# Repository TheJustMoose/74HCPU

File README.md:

# 74HCPU

Not a very scary instruction set discrete logic processor.

* 8 bit data
* 16 bit address / 64KB RAM
* 17 bit address (in V register) / 128KW Dual Bank Video RAM
* 16 [instructions](#instruction-list)
* 8 data [registers](#registers) and 4 pointer registers in 2 banks
* 1 [flags register](#flags-register) in IO port
* 32 input ports and 32 output ports (You can write a constant to the first 8 ports. Only registers can be written to the remaining ports.)
* Assembled from 74HCxx series ICs!

## Soft!
[ASM](./ASM.md)
[UEMUL]()

## CPU structure

## How this CPU works?

[Layers of PCBs](layers/README.md)

## Instruction list
*The words 'instruction' and 'command' mean the same thing.*

```
|----------------------------------------------|f|-------------------------------------------------------------|
|   HIGH BYTE    |    LOW BYTE   |  HIGH BYTE  |l|                                                             |
|F E D C  B A 9 8 7 6 5 4 3 2 1 0|   (again)   |a|                    SHORT DESCRIPTION                        |
|   4   +   3 + 1 + 3  +    5    = 16          |g|                                                             |
|----------------------------------------------|s|-------------------------------------------------------------|
|   ADD |  DST |1|    CONST or   | 01 0000 0001|*| Add a constant to a register (This is one command, not two) |
|   ADD |  DST |0| SRC |-|Z|z|I|i| 00 0000 0000|*| Add a register to a register (same OpCode, different bit 8) |
|----------------------------------------------| |-------------------------------------------------------------|
|  ADDC |  DST |C| SRC |F|Z|z|I|i| 10 0001 0000|*| ADD a constant or register and CARRY FLAG to a register     |
|   AND |  DST |C| SRC |-|Z|z|I|i| 20 0010 0000|*| Bitwise AND a constant or register with a register          |
|    OR |  DST |C| SRC |-|Z|z|I|i| 30 0011 0000|*| Bitwise OR a constant or register with a register           |
|   XOR |  DST |C| SRC |-|Z|z|I|i| 40 0100 0000|*| Bitwise XOR a constant or register with a register          |
|   MUL |  DST |C| SRC |-|Z|z|I|i| 50 0101 0000|*| MULtiply a constant or register by a register.              |
|   UNO |  DST |0|-|TYP|F|-|-|-|-| 60 0110 0000|*| Unary commands INV, SWAP, LSR, LSRC                         |
|   MOV |  DST |C| SRC |*|Z|z|I|i| 70 0111 0000| | MOV a constant or register to a register                    |
|   LPM |  DST |0|EXT|D|U|-|-|-|W| 80 1000 0000| | Load Program Memory - Read data from [commands] ROM         |
|    LD |  DST |V|EXT|D|U|OFFSET4| 90 1001 0000| | LoaD data from RAM to a register                            |
|    IN |  DST |  PORT   |Z|z|I|i| A0 1010 0000| | INput data from port to a register                          |
|--------------|8-7-6-5-4|-------|-------------| |-------------------------------------------------------------|
|   OUT | PORT |1|    CONST or   | B1 1011 0001| | Output const to a port (This is one command, not two)       |
|   OUT | PORT |0| SRC |PRT|X|O|o| B0 1011 0000| | Output register to a port (same OpCode, different bit 8)    |
|----------------------------------------------| |-------------------------------------------------------------|
|    ST |  SRC |V|EXT|D|U|OFFSET4| C0 1100 0000| | STore a register to a RAM                                   |
|   CMP |  DST |C| SRC |-|   -   | D0 1101 0000|+| CoMPare a constant or register with a register              |
|  CMPC |  DST |C| SRC |-|   -   | E0 1110 0000|+| Check flags then execute CMP                                |
| BRNCH |  CALL  | 8 bit OFFSET  | F0 1111 0000| | CALL a function with a relative address (offset)            |
| BRNCH |   JMP  | 8 bit OFFSET  | F1 1111 0001| | JMP to a relative address                                   |
| BRNCH |   RET  | 8 bit +STACK  | F2 1111 0010| | RETurn from function                                        |
| BRNCH |  RETI  | 8 bit OFFSET  | F3 1111 0011| | RETurn from Interrupt                                       |
| BRNCH |    JL  | 8 bit OFFSET  | F4 1111 0100| | Jump if Less                                                |
| BRNCH |    JE  | 8 bit OFFSET  | F5 1111 0101| | Jump if Equal                                               |
| BRNCH |   JNE  | 8 bit OFFSET  | F6 1111 0110| | Jump if Not Equal                                           |
| BRNCH |    JG  | 8 bit OFFSET  | F7 1111 0111| | Jump if greater                                             |
| BRNCH |    JZ  | 8 bit OFFSET  | F8 1111 1000| | Jump if Zero                                                |
| BRNCH |   JNZ  | 8 bit OFFSET  | F9 1111 1001| | Jump If Not Zero                                            |
| BRNCH |    JC  | 8 bit OFFSET  | FA 1111 1010| | Jump if Carry flag is set (one)                             |
| BRNCH |   JNC  | 8 bit OFFSET  | FB 1111 1011| | Jump if Carry flag is not set (zero)                        |
| BRNCH |   JHC  | 8 bit OFFSET  | FC 1111 1100| | Jump if Half Carry is set (one)                             |
| BRNCH |  JNHC  | 8 bit OFFSET  | FD 1111 1101| | Jump if Half Carry is not set (zero)                        |
| BRNCH | AFCALL | Hi 8 bit ADDR | FE 1111 1110| | Absolute Far Call (call a function at a 16-bit address)     |
| BRNCH |NOP/STOP|   1111 111x   | FF 1111 1111| | No OPeration (LSB is 0) or STOP CPU (LSB is 1)              |
|----------------------------------------------|-|-------------------------------------------------------------|
```
\* - means ZF, CF, HCF [flags](#flags-register), \+ - means GF, EQ, LF flags

### Registers
74HCPU has two register banks.
First bank has 8 arithmetic registers.
Second bank has 4 pointers (which can be used as 8 arithmetic registers).
You can change the active bank by writing BF bit of the [flags register](#flags-register).

#### Bank0 (8 pcs 8 bits registers):
|Name|Name|
|---|---|
|R7|R6|
|R5|R4|
|R3|R2|
|R1|R0|

#### Bank1 (4 pcs 16 bit registers):
<table>
<tr>
<td>

|Name|Usage|
|---|---|
|V|Video Pointer (**17** bits)|
|SP|Stack Pointer (16 bits)|
|Y|Pointer 1 (16 bits), e.g. Destination|
|X|Pointer 0 (16 bits), e.g. Source|
16 bit pointers
</td>
<td>

|Name|Name|
|---|---|
|VH|VL|
|SPH|SPL|
|YH|YL|
|XH|XL|
or 8 bit registers
</td></tr>
</table>

Also, you can use the registers of bank 1 in the same way as bank 0: R0, R1, ... R7
(R7 will store the high half of SP, R6 the low half).

### Flags register
|Bit|Flag Name|Usage|Reason|
|---|---|---|---|
|7|-|reserved|-|
|6|BF|Bank|You can write it|
|5|GF|Greater|Compare (CMP)|
|4|~EQ|Equal (inverted)|Compare (CMP)|
|3|LF|Less|Compare (CMP)|
|2|ZF|Zero|Arithmetic|
|1|CF|Carry|Arithmetic|
|0|HCF|Half Carry|Arithmetic|

### ADD, ADDC, AND, OR, XOR, MUL are binary commands  
You can use it:  
CMD Rd, Rs  
Where Rd is destination register.  
And Rs is source register.  
These commands work like this:  
Rd := Rd CMD Rs  
For example, ADD command does this:  
ADD R0, R1 -> R0 := R0 + R1  
Also you can use immediate value:  
CMD Rd, CONST  
(You can use CONST with any command: ADD, ADDC, AND, OR, XOR, MUL, MOV...)

The only exception to the use of the Rd register is MUL command.  
A pair of registers is needed to store the multiplication results.  
For example:  
MUL R1, R2 will store result into R1:R0 pair.  
That is, R1:R0 := R1 * R2.

### MUL Examples
```
  Rd select output Pair:
      _________
  Rd /         \ Pair   Rd   Rs
     |         \/
MUL R0, R1 -> R1:R0  := R0 * R1
MUL R1, R0 -> R1:R0  := R1 * R0
MUL R1, R2 -> R1:R0  := R1 * R2
MUL R1, R7 -> R1:R0  := R1 * R7
MUL R2, R3 -> R3:R2  := R2 * R3
MUL R2, R7 -> R3:R2  := R2 * R7
....
```

#### Register pairs  
The MUL command uses the following register pairs to store result:  
R1:R0 (when Rd is R0 or R1)  
R3:R2 (when Rd is R2 or R3)  
R5:R4 (when Rd is R4 or R5)  
R7:R6 (when Rd is R6 or R7)  
Rd is used to select output register pair.

### Instruction options  
C - Low byte [of command] contains constant value (1) or options (0).  
Z - Will reset high nibble of SRC register before use.  
z - Will reset low nibble of SRC register before use.  
I - Will invert high nibble of SRC register before use.  
i - Will invert low nibble of SRC register before use.  
F - Set CF flag to TRUE while executing command.  
W - Command will work with word, not byte.  
V - Command will work with Video RAM.  
D - Down, decrease pointer after command.  
U - Up, increase pointer after command.  
OFFSET4 - 4 bit size int offset to current pointer.  
O - Out will write to high nibble of port.  
o - Out will write to low nibble of port.  
X - Out will toggle bits of port by mask in register.  
SRC - Index of source register (0-7).  
DST - Index of destination register (0-7).  
TYP - Kind of unary operation (0-3).  
EXT - Index of pointer register (0-3).  
PORT + PRT - 5 bit of port index.

### UNO - unary commands  
There are four unary commands: LSR, LSRC, INV, SWAP.  
LSR shift register bits to the right. CF flag get value of right (low) bit.  
LSRC do same, but left (high) bit get value of CF.  
SWAP simply swap the nibbles.  
INV simply invert all the bits.

### LPM - Load Program Memory  
This command read (1 byte of) data from ROM, not RAM. And this command write data to register.  
The data stores in the same ROM that stores the commands themselves.
Also you can use LPMW to read the whole 16 bit word from ROM and store data to [register pair](#register-pairs).

### LD, ST - Memory commands  
LD - LoaD data from memory  
ST - STore data to memory  
V - 0 for RAM and 1 for Video RAM  
SRC - register to read  
DST - register to write  
EXT - register pair which store pointer to memory  
D - Decrement pointer after use  
U - Increment pointer after use  
OFFSET4 - 4 bit integer offset (-8...+7)  
(CPU will read/write memory with address ptr(EXT) + OFFSET4)  
Examples:
```
LD R0, X    ; read memory data from X pointer into the R0 register
ST Y, R1    ; write data from R1 into memory with address from Y pointer
ST YI, R1   ; write data and increment Y pointer
ST YD, R1   ; write data and decrement Y pointer
ST Y+5, R1  ; write data into memory address Y+5
LDV R7, V   ; read data from Video RAM with address V and store it into R7 (R7:R6 pair)
LDV R7, V+1 ; **disabled** command, you can use displacement only with X, Y and SP pointers
```

### BRNCH - Branch commands  
CALL - call a function by offset  
AFCALL - call a function to an absolute address  
RET - return to the address stored on the stack  
RETI - return from interrupt to the address stored on the stack  
JMP - go by offset  
NOP - no operation (do nothing)  
STOP - the processor will stop executing the program  
JL, JE, JNE, JG, JZ, JNZ, JC, JNC, JHC, JNHC - conditional jump instructions  
JL - jump if less  
JE - jump if equal  
JNE - jump if not equal  
JG - jump if greater  
JZ - jump if zero  
JNZ - jump if not zero  
JC - jump if carry  
JNC - jump if not carry  
JHC - jump if half carry  
JNHC - jump if not half carry

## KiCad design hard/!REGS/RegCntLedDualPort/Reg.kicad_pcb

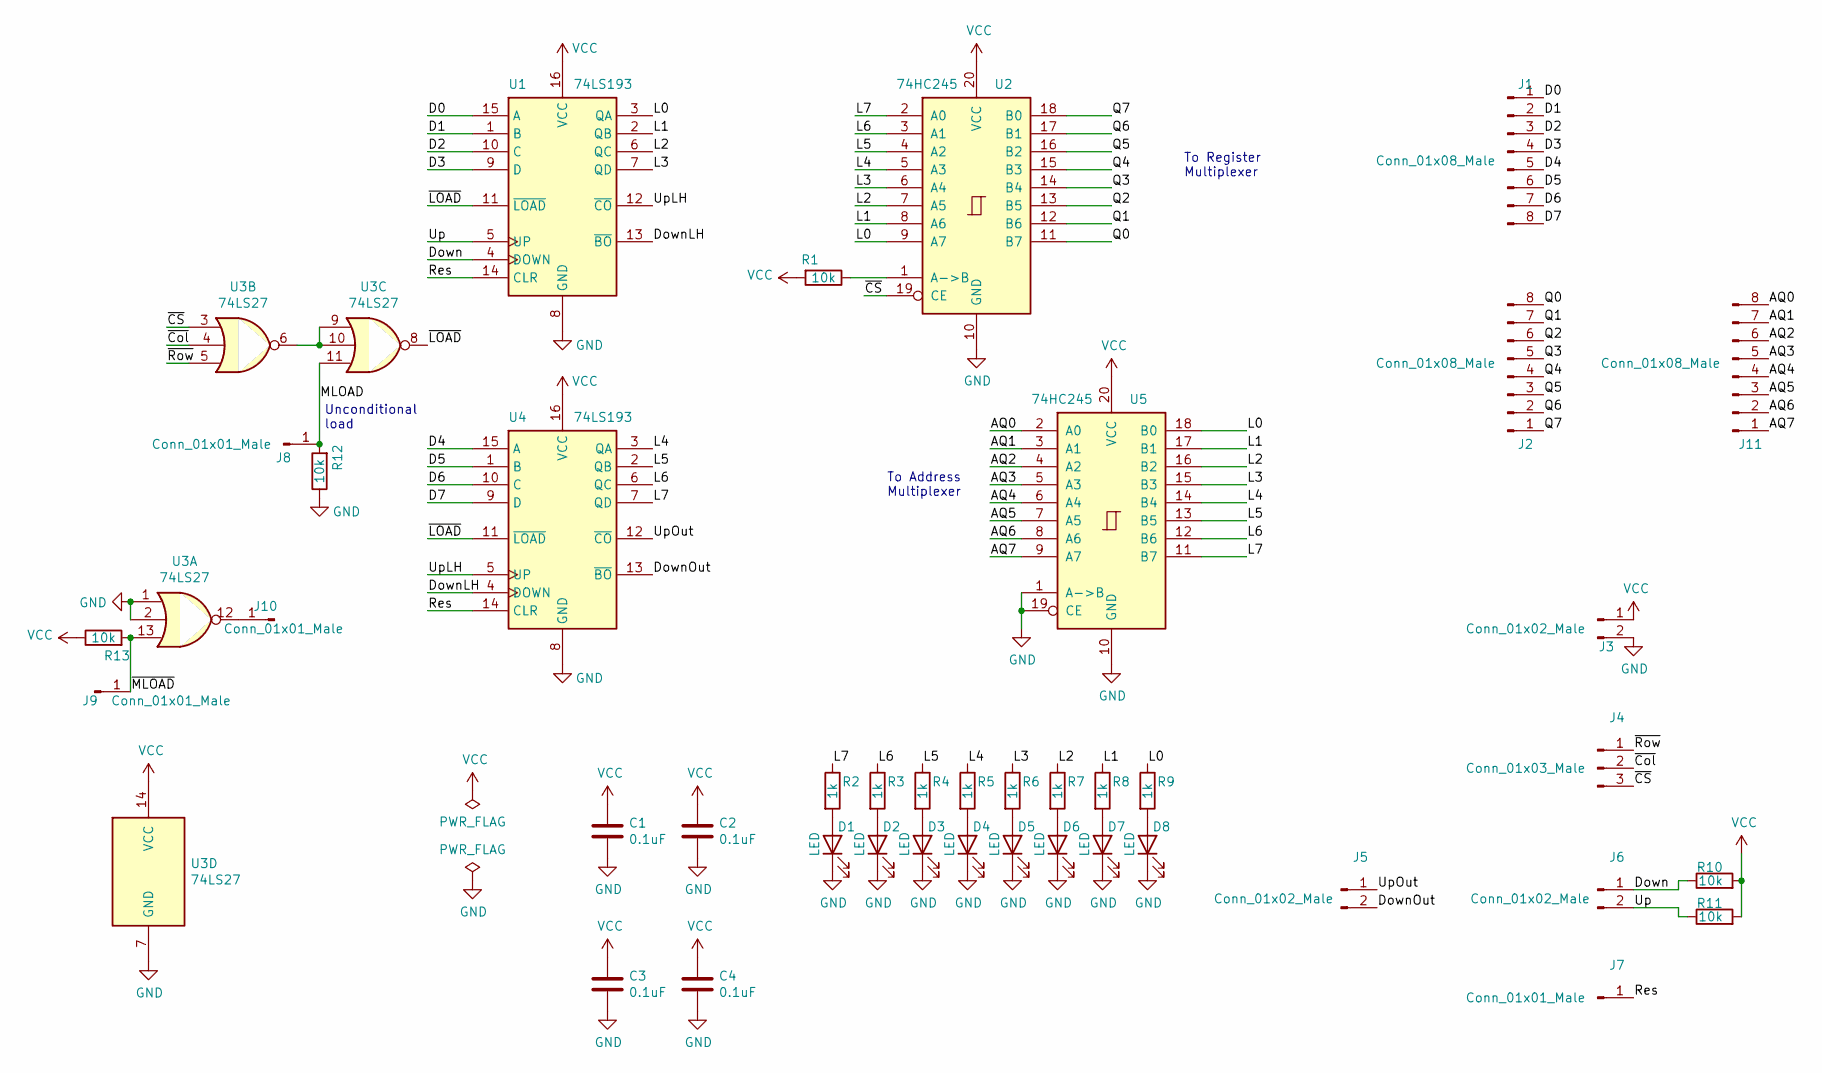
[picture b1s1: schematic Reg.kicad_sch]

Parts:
C1, C3: 0.1uF; C_Axial_L3.8mm_D2.6mm_P12.50mm_Horizontal
C2, C4: 0.1uF; C_0805_2012Metric_Pad1.18x1.45mm_HandSolder
D1, D2, D3, D4, D5, D6, D7, D8: LED; LED_0805_2012Metric_Pad1.15x1.40mm_HandSolder
J1, J2, J11: Conn_01x08_Male; PinHeader_1x08_P2.54mm_Horizontal
J3, J5, J6: Conn_01x02_Male; PinHeader_1x02_P2.54mm_Horizontal
J4: Conn_01x03_Male; PinHeader_1x03_P2.54mm_Horizontal
J7, J8, J9, J10: Conn_01x01_Male; PinHeader_1x01_P2.54mm_Horizontal
R1, R10, R11, R12, R13: 10k; R_0805_2012Metric_Pad1.20x1.40mm_HandSolder
R2, R3, R4, R5, R6, R7, R8, R9: 1k; R_0805_2012Metric_Pad1.20x1.40mm_HandSolder
U1, U4: 74LS193; SOP-16_3.9x9.9mm_P1.27mm
U2, U5: 74HC245; SOP-20_7.5x12.8mm_P1.27mm
U3: 74LS27; SO-14_3.9x8.65mm_P1.27mm

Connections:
/AQ0: J11.8, U5.2 (A0)
/AQ1: J11.7, U5.3 (A1)
/AQ2: J11.6, U5.4 (A2)
/AQ3: J11.5, U5.5 (A3)
/AQ4: J11.4, U5.6 (A4)
/AQ5: J11.3, U5.7 (A5)
/AQ6: J11.2, U5.8 (A6)
/AQ7: J11.1, U5.9 (A7)
/D0: J1.1, U1.15 (A)
/D1: J1.2, U1.1 (B)
/D2: J1.3, U1.10 (C)
/D3: J1.4, U1.9 (D)
/D4: J1.5, U4.15 (A)
/D5: J1.6, U4.1 (B)
/D6: J1.7, U4.10 (C)
/D7: J1.8, U4.9 (D)
/Down: J6.1, R10.1, U1.4 (DOWN)
/DownLH: U1.13 (~BO), U4.4 (DOWN)
/DownOut: J5.2, U4.13 (~BO)
/L0: R9.1, U1.3 (QA), U2.9 (A7), U5.18 (B0)
/L1: R8.1, U1.2 (QB), U2.8 (A6), U5.17 (B1)
/L2: R7.1, U1.6 (QC), U2.7 (A5), U5.16 (B2)
/L3: R6.1, U1.7 (QD), U2.6 (A4), U5.15 (B3)
/L4: R5.1, U2.5 (A3), U4.3 (QA), U5.14 (B4)
/L5: R4.1, U2.4 (A2), U4.2 (QB), U5.13 (B5)
/L6: R3.1, U2.3 (A1), U4.6 (QC), U5.12 (B6)
/L7: R2.1, U2.2 (A0), U4.7 (QD), U5.11 (B7)
/MLOAD: J8.1, R12.2, U3.11
/Q0: J2.8, U2.11 (B7)
/Q1: J2.7, U2.12 (B6)
/Q2: J2.6, U2.13 (B5)
/Q3: J2.5, U2.14 (B4)
/Q4: J2.4, U2.15 (B3)
/Q5: J2.3, U2.16 (B2)
/Q6: J2.2, U2.17 (B1)
/Q7: J2.1, U2.18 (B0)
/Res: J7.1, U1.14 (CLR), U4.14 (CLR)
/Up: J6.2, R11.1, U1.5 (UP)
/UpLH: U1.12 (~CO), U4.5 (UP)
/UpOut: J5.1, U4.12 (~CO)
/~CS: J4.3, U2.19 (CE), U3.3
/~Col: J4.2, U3.4
/~LOAD: U1.11 (~LOAD), U3.8, U4.11 (~LOAD)
/~MLOAD: J9.1, R13.2, U3.13
/~Row: J4.1, U3.5
GND: C1.2, C2.2, C3.2, C4.2, D1.1 (K), D2.1 (K), D3.1 (K), D4.1 (K), D5.1 (K), D6.1 (K), D7.1 (K), D8.1 (K), J3.2, R12.1, U1.8 (GND), U2.10 (GND), U3.1, U3.2, U3.7 (GND), U4.8 (GND), U5.1 (A->B), U5.10 (GND), U5.19 (CE)
unnamed: D1.2 (A), R2.2
unnamed: D2.2 (A), R3.2
unnamed: D3.2 (A), R4.2
unnamed: D4.2 (A), R5.2
unnamed: D5.2 (A), R6.2
unnamed: D6.2 (A), R7.2
unnamed: D7.2 (A), R8.2
unnamed: D8.2 (A), R9.2
unnamed: J10.1, U3.12
unnamed: R1.1, U2.1 (A->B)
unnamed: U3.6, U3.9, U3.10
VCC: C1.1, C2.1, C3.1, C4.1, J3.1, R1.2, R10.2, R11.2, R13.1, U1.16 (VCC), U2.20 (VCC), U3.14 (VCC), U4.16 (VCC), U5.20 (VCC)

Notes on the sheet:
To Register Multiplexer
To Address Multiplexer
Unconditional load

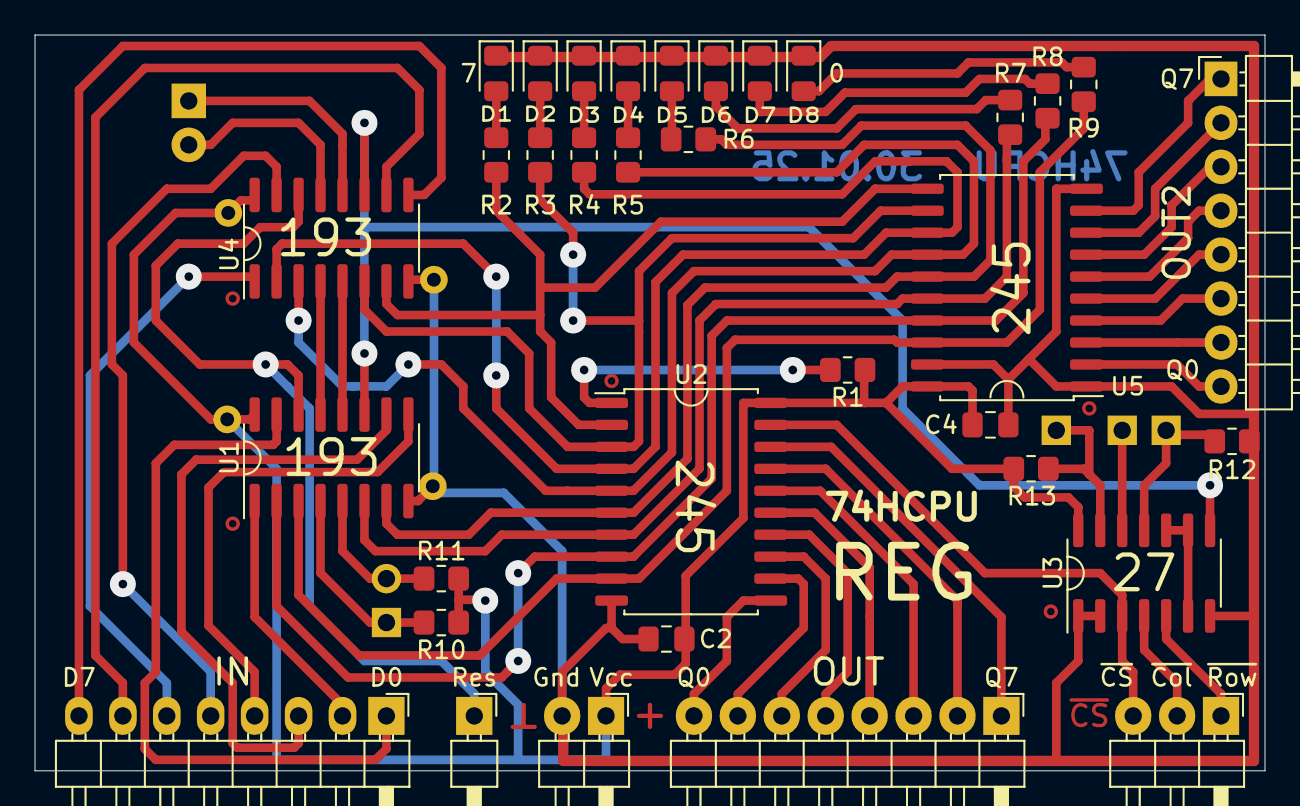
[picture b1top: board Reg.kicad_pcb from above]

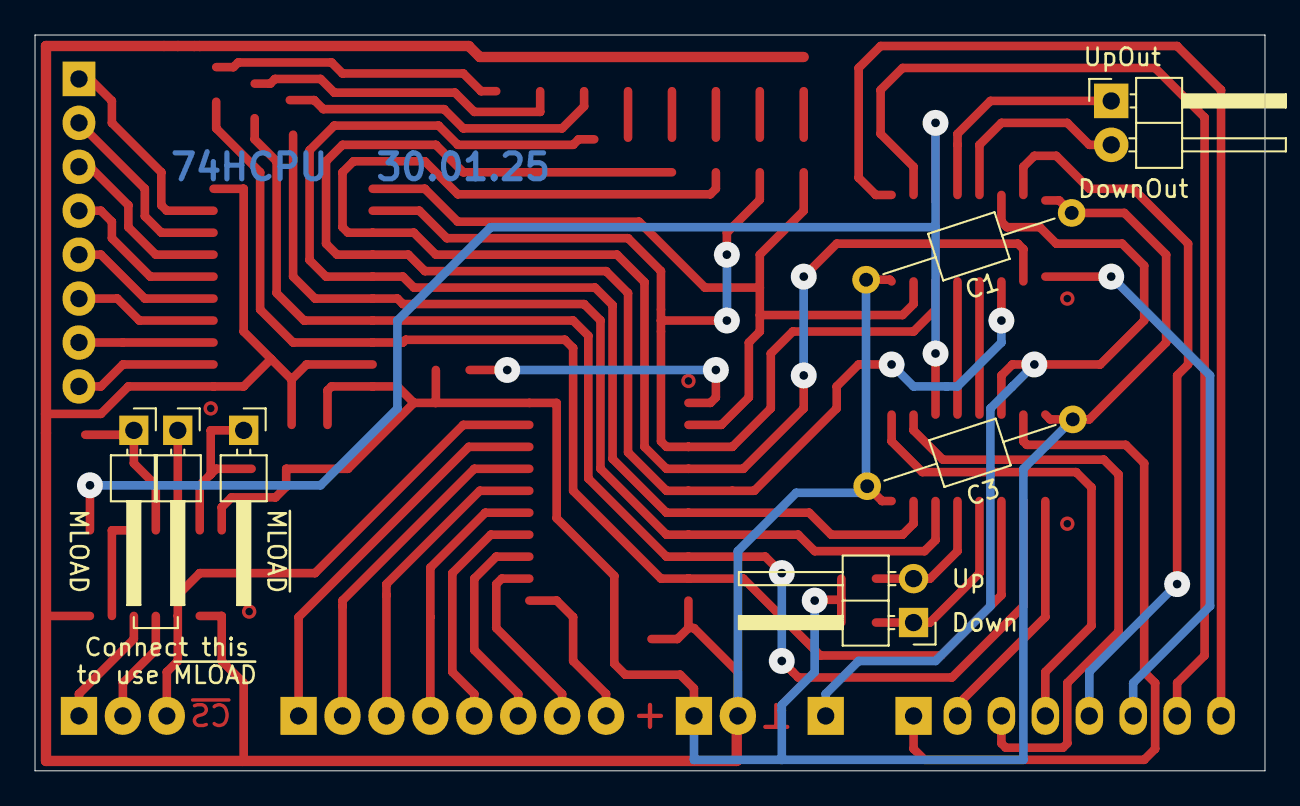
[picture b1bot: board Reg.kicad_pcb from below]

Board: 2 copper layers, 71.1 x 42.5 mm, 41 parts (7 on the bottom side), 58 nets.

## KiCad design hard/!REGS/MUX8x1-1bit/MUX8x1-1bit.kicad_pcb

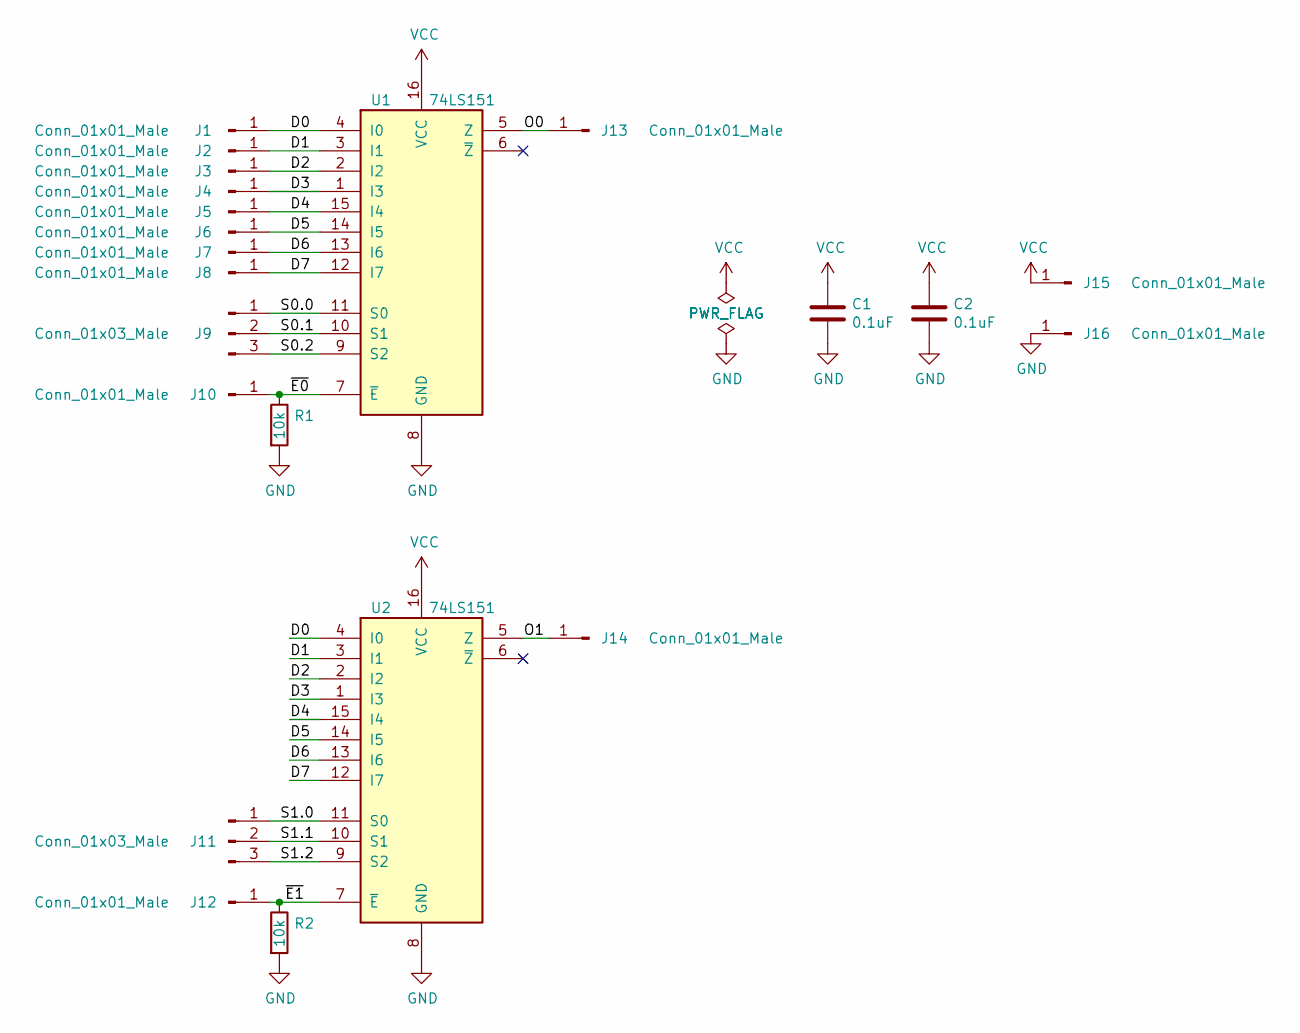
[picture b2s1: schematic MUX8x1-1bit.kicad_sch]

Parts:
C1, C2: 0.1uF; C_0805_2012Metric_Pad1.18x1.45mm_HandSolder
J1, J2, J3, J4, J5, J6, J7, J8, J10, J12, J13, J14, J15, J16: Conn_01x01_Male; PinHeader_1x01_P2.54mm_Horizontal
J9, J11: Conn_01x03_Male; PinHeader_1x03_P2.54mm_Horizontal
R1, R2: 10k; R_0805_2012Metric_Pad1.20x1.40mm_HandSolder
U1, U2: 74LS151; SO-16_3.9x9.9mm_P1.27mm

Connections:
/D0: J1.1, U1.4 (I0), U2.4 (I0)
/D1: J2.1, U1.3 (I1), U2.3 (I1)
/D2: J3.1, U1.2 (I2), U2.2 (I2)
/D3: J4.1, U1.1 (I3), U2.1 (I3)
/D4: J5.1, U1.15 (I4), U2.15 (I4)
/D5: J6.1, U1.14 (I5), U2.14 (I5)
/D6: J7.1, U1.13 (I6), U2.13 (I6)
/D7: J8.1, U1.12 (I7), U2.12 (I7)
/O0: J13.1, U1.5 (Z)
/O1: J14.1, U2.5 (Z)
/S0.0: J9.1, U1.11 (S0)
/S0.1: J9.2, U1.10 (S1)
/S0.2: J9.3, U1.9 (S2)
/S1.0: J11.1, U2.11 (S0)
/S1.1: J11.2, U2.10 (S1)
/S1.2: J11.3, U2.9 (S2)
/~E0: J10.1, R1.1, U1.7 (~E)
/~E1: J12.1, R2.1, U2.7 (~E)
GND: C1.2, C2.2, J16.1, R1.2, R2.2, U1.8 (GND), U2.8 (GND)
VCC: C1.1, C2.1, J15.1, U1.16 (VCC), U2.16 (VCC)

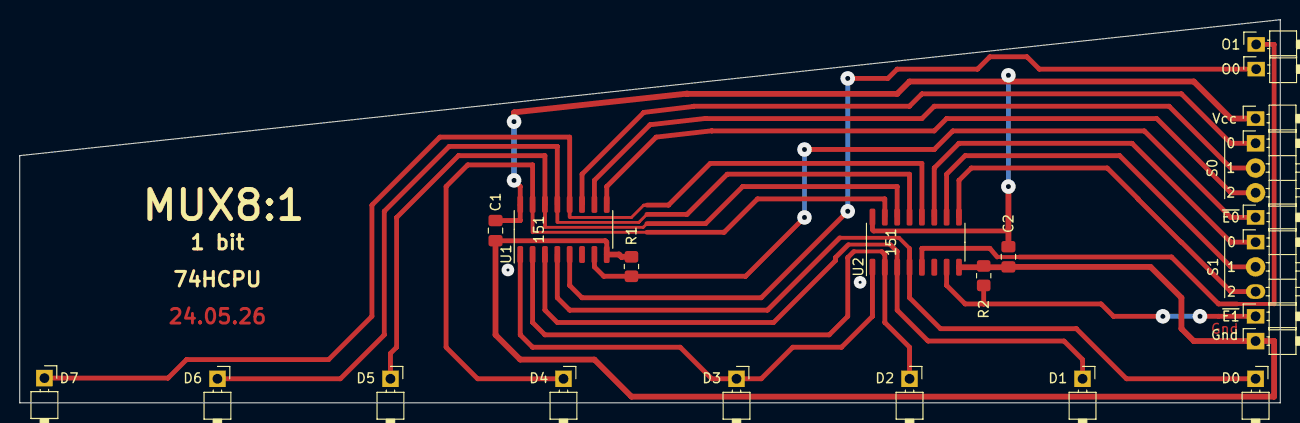
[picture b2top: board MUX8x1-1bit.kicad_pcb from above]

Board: 2 copper layers, 129.5 x 39.4 mm, 22 parts (0 on the bottom side), 20 nets.

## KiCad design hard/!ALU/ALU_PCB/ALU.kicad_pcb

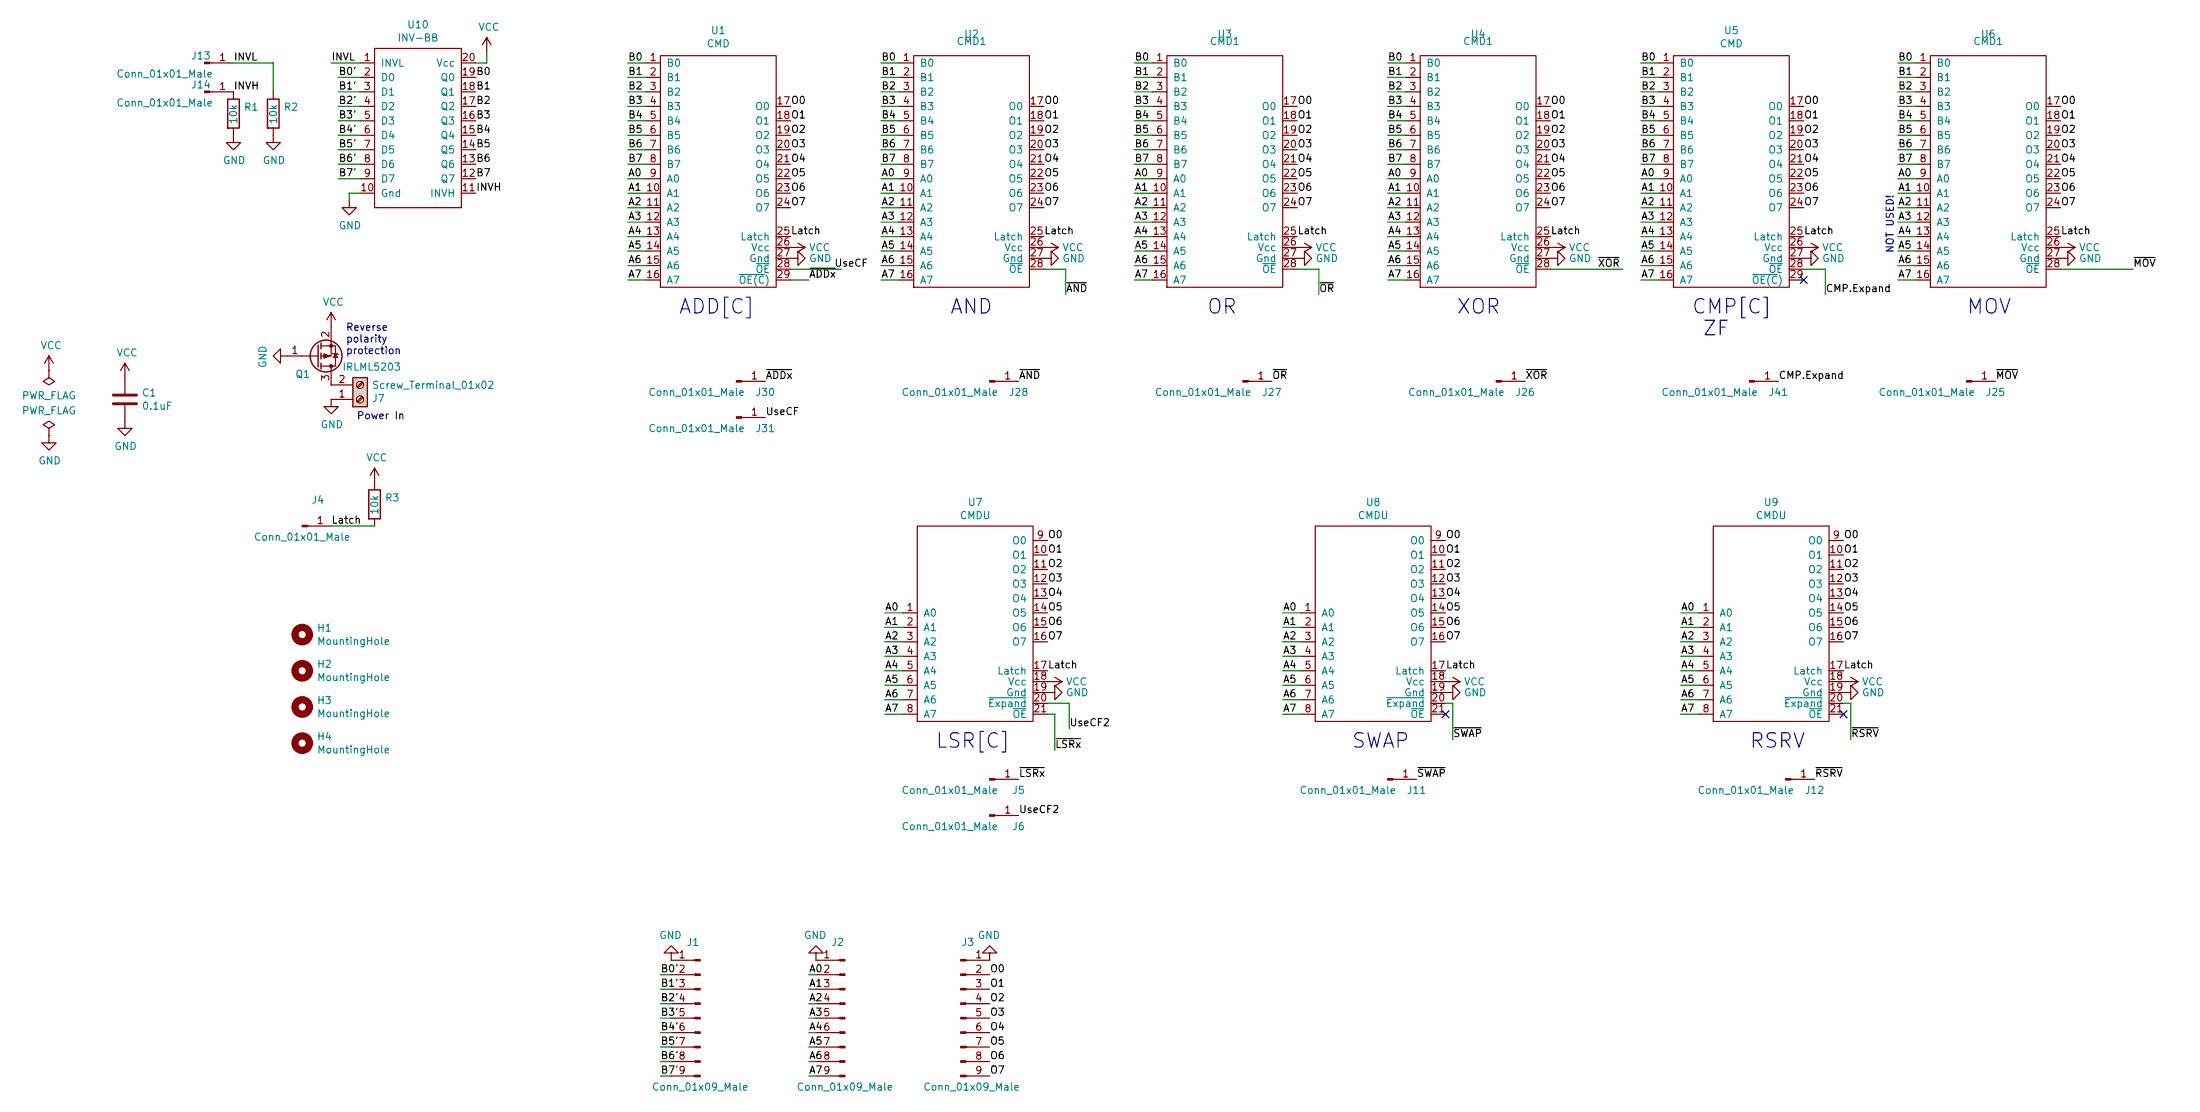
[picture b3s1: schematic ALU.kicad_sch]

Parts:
C1: 0.1uF; C_0805_2012Metric_Pad1.18x1.45mm_HandSolder
H1, H2, H3, H4: MountingHole; MountingHole_3.2mm_M3
J1, J2, J3: Conn_01x09_Male; PinHeader_1x09_P2.54mm_Vertical
J4, J5, J6, J11, J12, J13, J14, J25, J26, J27, J28, J30, J31, J41: Conn_01x01_Male; PinHeader_1x01_P2.54mm_Vertical
J7: Screw_Terminal_01x02; TerminalBlock_Phoenix_MKDS-1,5-2_1x02_P5.00mm_Horizontal
Q1: IRLML5203; SOT-23
R1, R2, R3: 10k; R_0805_2012Metric_Pad1.20x1.40mm_HandSolder
U1, U5: CMD
U2, U3, U4, U6: CMD1; CMDwoC
U7, U8, U9: CMDU
U10: INV-BB; INV-B

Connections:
/A0: J2.2, U1.9 (A0), U2.9 (A0), U3.9 (A0), U4.9 (A0), U5.9 (A0), U6.9 (A0), U7.1 (A0), U8.1 (A0), U9.1 (A0)
/A1: J2.3, U1.10 (A1), U2.10 (A1), U3.10 (A1), U4.10 (A1), U5.10 (A1), U6.10 (A1), U7.2 (A1), U8.2 (A1), U9.2 (A1)
/A2: J2.4, U1.11 (A2), U2.11 (A2), U3.11 (A2), U4.11 (A2), U5.11 (A2), U6.11 (A2), U7.3 (A2), U8.3 (A2), U9.3 (A2)
/A3: J2.5, U1.12 (A3), U2.12 (A3), U3.12 (A3), U4.12 (A3), U5.12 (A3), U6.12 (A3), U7.4 (A3), U8.4 (A3), U9.4 (A3)
/A4: J2.6, U1.13 (A4), U2.13 (A4), U3.13 (A4), U4.13 (A4), U5.13 (A4), U6.13 (A4), U7.5 (A4), U8.5 (A4), U9.5 (A4)
/A5: J2.7, U1.14 (A5), U2.14 (A5), U3.14 (A5), U4.14 (A5), U5.14 (A5), U6.14 (A5), U7.6 (A5), U8.6 (A5), U9.6 (A5)
/A6: J2.8, U1.15 (A6), U2.15 (A6), U3.15 (A6), U4.15 (A6), U5.15 (A6), U6.15 (A6), U7.7 (A6), U8.7 (A6), U9.7 (A6)
/A7: J2.9, U1.16 (A7), U2.16 (A7), U3.16 (A7), U4.16 (A7), U5.16 (A7), U6.16 (A7), U7.8 (A7), U8.8 (A7), U9.8 (A7)
/B0: U1.1 (B0), U2.1 (B0), U3.1 (B0), U4.1 (B0), U5.1 (B0), U6.1 (B0), U10.19 (Q0)
/B0': J1.2, U10.2 (D0)
/B1: U1.2 (B1), U2.2 (B1), U3.2 (B1), U4.2 (B1), U5.2 (B1), U6.2 (B1), U10.18 (Q1)
/B1': J1.3, U10.3 (D1)
/B2: U1.3 (B2), U2.3 (B2), U3.3 (B2), U4.3 (B2), U5.3 (B2), U6.3 (B2), U10.17 (Q2)
/B2': J1.4, U10.4 (D2)
/B3: U1.4 (B3), U2.4 (B3), U3.4 (B3), U4.4 (B3), U5.4 (B3), U6.4 (B3), U10.16 (Q3)
/B3': J1.5, U10.5 (D3)
/B4: U1.5 (B4), U2.5 (B4), U3.5 (B4), U4.5 (B4), U5.5 (B4), U6.5 (B4), U10.15 (Q4)
/B4': J1.6, U10.6 (D4)
/B5: U1.6 (B5), U2.6 (B5), U3.6 (B5), U4.6 (B5), U5.6 (B5), U6.6 (B5), U10.14 (Q5)
/B5': J1.7, U10.7 (D5)
/B6: U1.7 (B6), U2.7 (B6), U3.7 (B6), U4.7 (B6), U5.7 (B6), U6.7 (B6), U10.13 (Q6)
/B6': J1.8, U10.8 (D6)
/B7: U1.8 (B7), U2.8 (B7), U3.8 (B7), U4.8 (B7), U5.8 (B7), U6.8 (B7), U10.12 (Q7)
/B7': J1.9, U10.9 (D7)
/CMP.Expand: J41.1, U5.28 (~OE)
/INVH: J14.1, R1.1, U10.11 (INVH)
/INVL: J13.1, R2.1, U10.1 (INVL)
/Latch: J4.1, R3.2, U1.25 (Latch), U2.25 (Latch), U3.25 (Latch), U4.25 (Latch), U5.25 (Latch), U6.25 (Latch), U7.17 (Latch), U8.17 (Latch), U9.17 (Latch)
/O0: J3.2, U1.17 (O0), U2.17 (O0), U3.17 (O0), U4.17 (O0), U5.17 (O0), U6.17 (O0), U7.9 (O0), U8.9 (O0), U9.9 (O0)
/O1: J3.3, U1.18 (O1), U2.18 (O1), U3.18 (O1), U4.18 (O1), U5.18 (O1), U6.18 (O1), U7.10 (O1), U8.10 (O1), U9.10 (O1)
/O2: J3.4, U1.19 (O2), U2.19 (O2), U3.19 (O2), U4.19 (O2), U5.19 (O2), U6.19 (O2), U7.11 (O2), U8.11 (O2), U9.11 (O2)
/O3: J3.5, U1.20 (O3), U2.20 (O3), U3.20 (O3), U4.20 (O3), U5.20 (O3), U6.20 (O3), U7.12 (O3), U8.12 (O3), U9.12 (O3)
/O4: J3.6, U1.21 (O4), U2.21 (O4), U3.21 (O4), U4.21 (O4), U5.21 (O4), U6.21 (O4), U7.13 (O4), U8.13 (O4), U9.13 (O4)
/O5: J3.7, U1.22 (O5), U2.22 (O5), U3.22 (O5), U4.22 (O5), U5.22 (O5), U6.22 (O5), U7.14 (O5), U8.14 (O5), U9.14 (O5)
/O6: J3.8, U1.23 (O6), U2.23 (O6), U3.23 (O6), U4.23 (O6), U5.23 (O6), U6.23 (O6), U7.15 (O6), U8.15 (O6), U9.15 (O6)
/O7: J3.9, U1.24 (O7), U2.24 (O7), U3.24 (O7), U4.24 (O7), U5.24 (O7), U6.24 (O7), U7.16 (O7), U8.16 (O7), U9.16 (O7)
/UseCF: J31.1, U1.28 (~OE)
/UseCF2: J6.1, U7.20 (~Expand)
/~ADDx: J30.1, U1.29 (~OE(C))
/~AND: J28.1, U2.28 (~OE)
/~LSRx: J5.1, U7.21 (~OE)
/~MOV: J25.1, U6.28 (~OE)
/~OR: J27.1, U3.28 (~OE)
/~RSRV: J12.1, U9.20 (~Expand)
/~SWAP: J11.1, U8.20 (~Expand)
/~XOR: J26.1, U4.28 (~OE)
GND: C1.2, J1.1, J2.1, J3.1, J7.1, Q1.1 (G), R1.2, R2.2, U1.27 (Gnd), U2.27 (Gnd), U3.27 (Gnd), U4.27 (Gnd), U5.27 (Gnd), U6.27 (Gnd), U7.19 (Gnd), U8.19 (Gnd), U9.19 (Gnd), U10.10 (Gnd)
unnamed: J7.2, Q1.3 (D)
VCC: C1.1, Q1.2 (S), R3.1, U1.26 (Vcc), U2.26 (Vcc), U3.26 (Vcc), U4.26 (Vcc), U5.26 (Vcc), U6.26 (Vcc), U7.18 (Vcc), U8.18 (Vcc), U9.18 (Vcc), U10.20 (Vcc)

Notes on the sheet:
ADD[C]
Power In
MOV
RSRV
SWAP
NOT USED!
AND
XOR
Reverse polarity protection
CMP[C]
LSR[C]

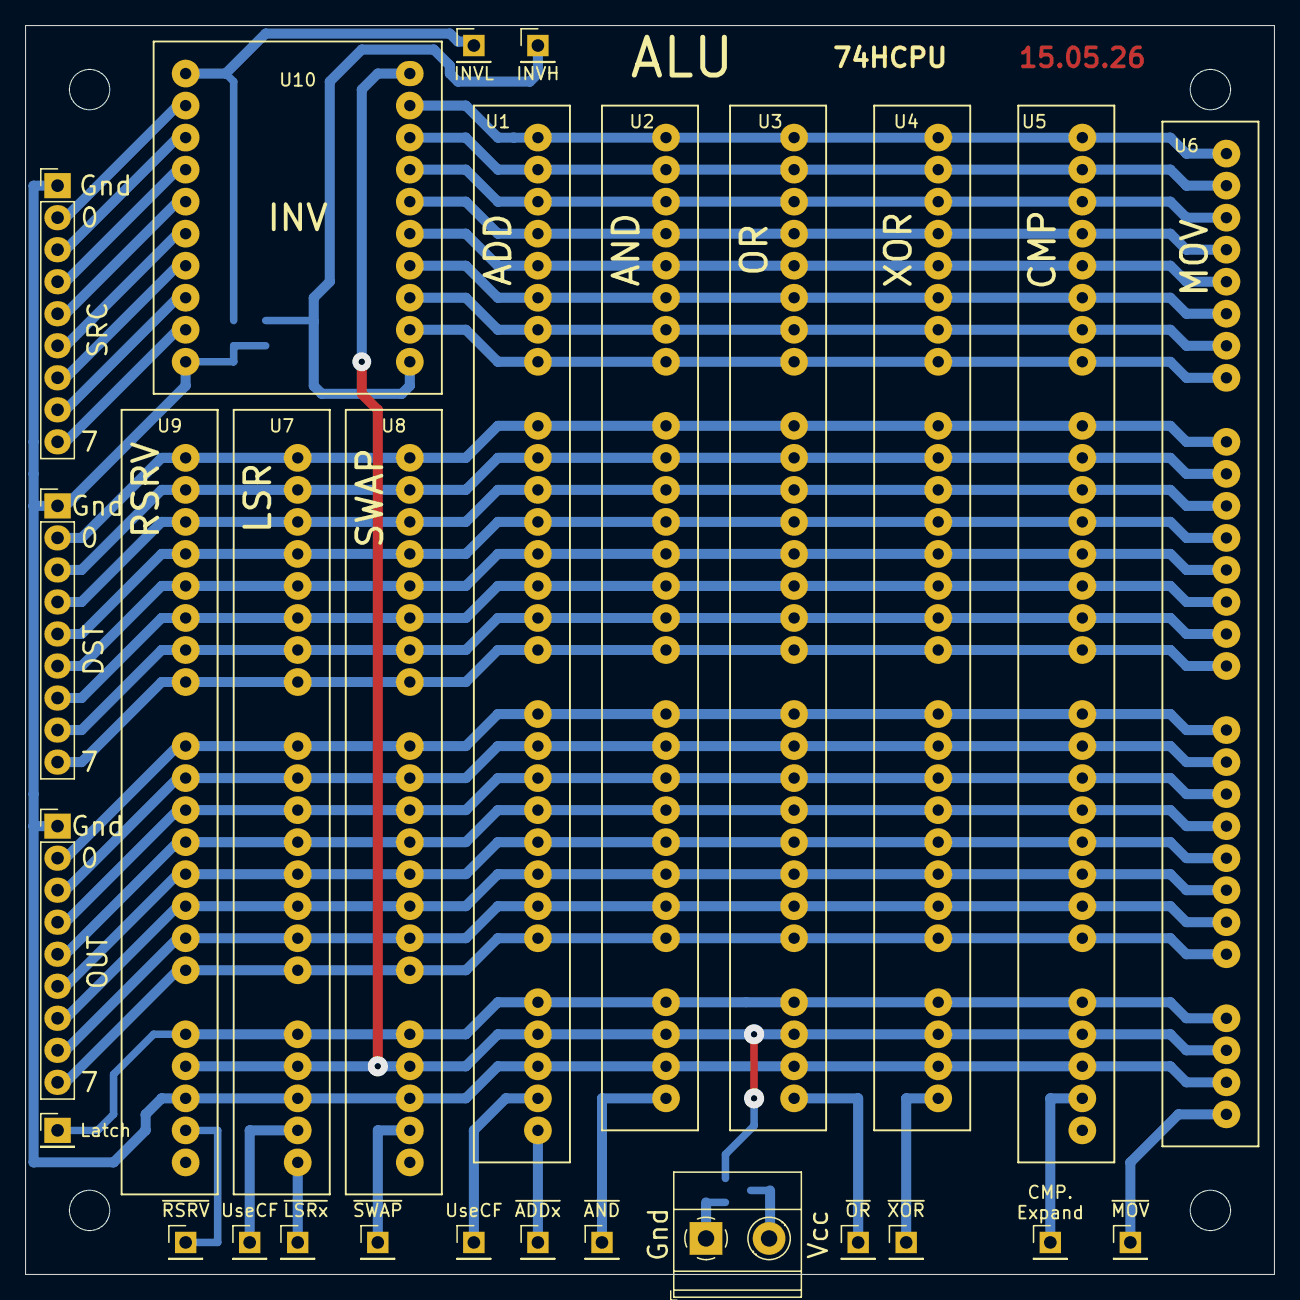
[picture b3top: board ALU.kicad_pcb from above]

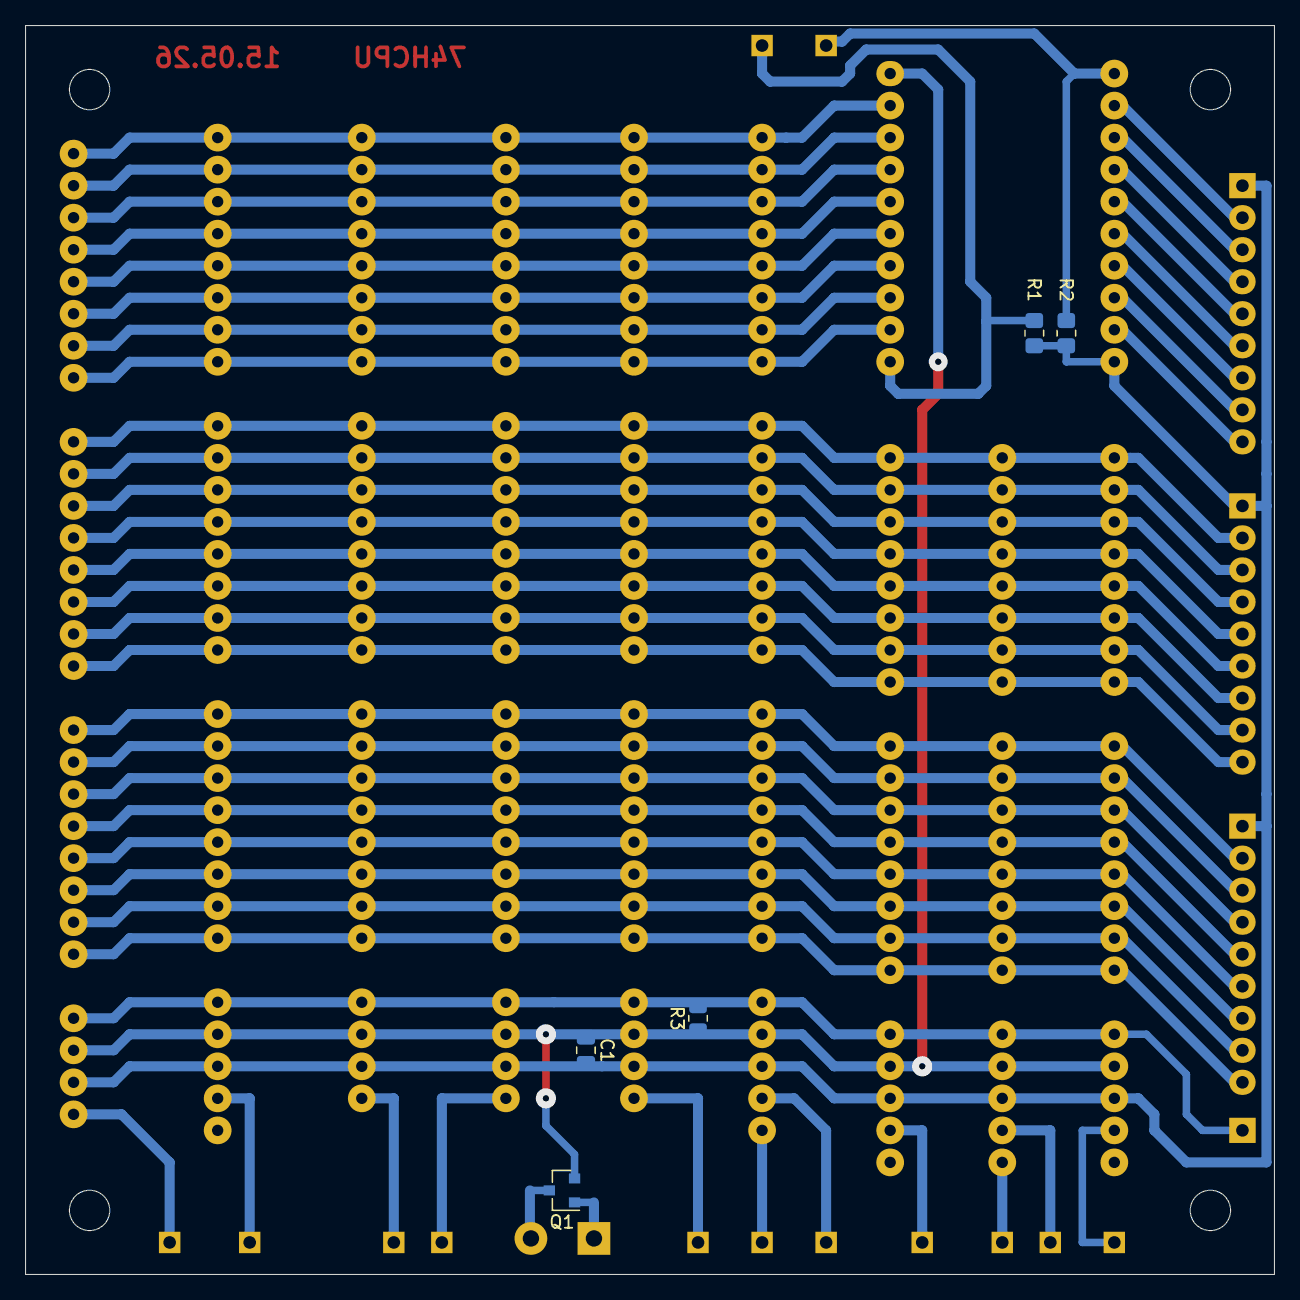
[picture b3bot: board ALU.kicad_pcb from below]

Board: 2 copper layers, 99.1 x 99.1 mm, 37 parts (5 on the bottom side), 49 nets.

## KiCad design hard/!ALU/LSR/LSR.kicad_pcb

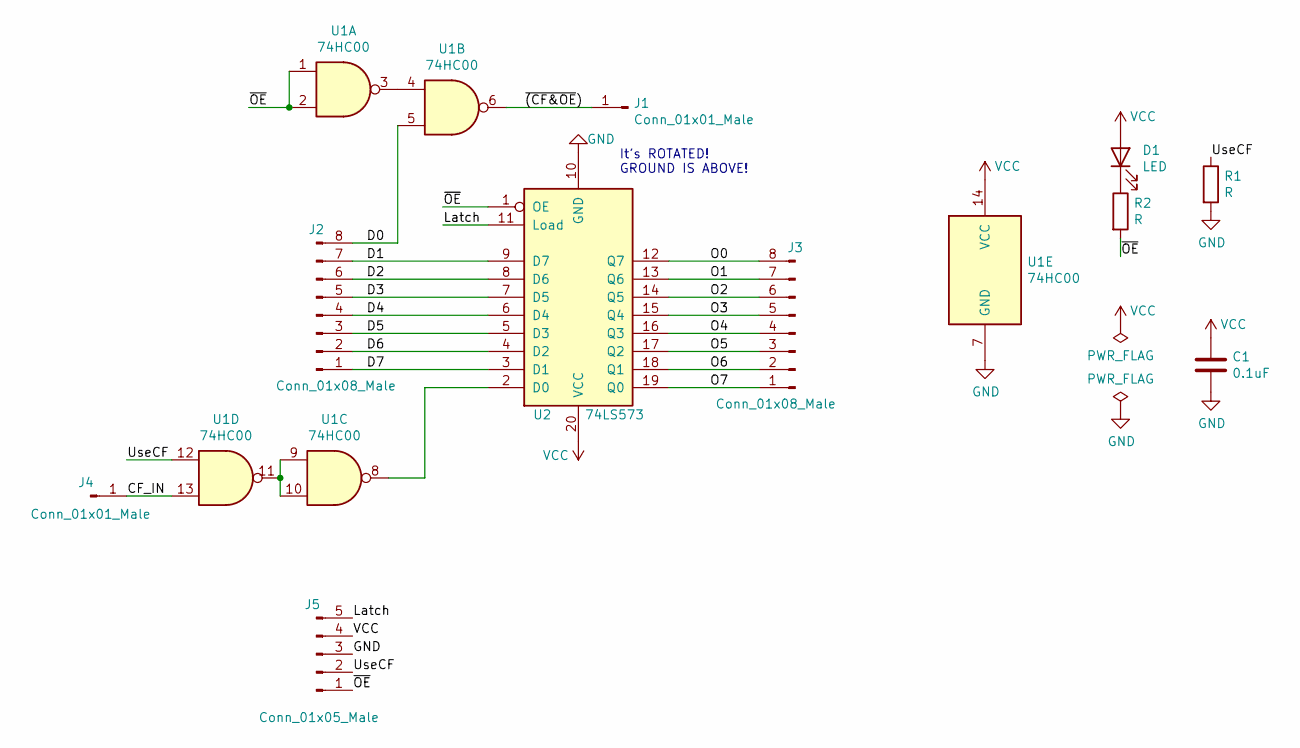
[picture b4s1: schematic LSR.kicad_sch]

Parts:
C1: 0.1uF; C_0805_2012Metric_Pad1.18x1.45mm_HandSolder
D1: LED; LED_0805_2012Metric_Pad1.15x1.40mm_HandSolder
J1, J4: Conn_01x01_Male; PinHeader_1x01_P2.54mm_Vertical
J2, J3: Conn_01x08_Male; PinHeader_1x08_P2.54mm_Horizontal
J5: Conn_01x05_Male; PinHeader_1x05_P2.54mm_Horizontal
R1, R2: R; R_0805_2012Metric_Pad1.20x1.40mm_HandSolder
U1: 74HC00; SO-14_3.9x8.65mm_P1.27mm
U2: 74LS573; SOIC-20W_7.5x12.8mm_P1.27mm

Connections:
/CF_IN: J4.1, U1.13
/D0: J2.8, U1.5
/D1: J2.7, U2.9 (D7)
/D2: J2.6, U2.8 (D6)
/D3: J2.5, U2.7 (D5)
/D4: J2.4, U2.6 (D4)
/D5: J2.3, U2.5 (D3)
/D6: J2.2, U2.4 (D2)
/D7: J2.1, U2.3 (D1)
/Latch: J5.5, U2.11 (Load)
/O0: J3.8, U2.12 (Q7)
/O1: J3.7, U2.13 (Q6)
/O2: J3.6, U2.14 (Q5)
/O3: J3.5, U2.15 (Q4)
/O4: J3.4, U2.16 (Q3)
/O5: J3.3, U2.17 (Q2)
/O6: J3.2, U2.18 (Q1)
/O7: J3.1, U2.19 (Q0)
/UseCF: J5.2, R1.1, U1.12
/~(CF&OE): J1.1, U1.6
/~OE: J5.1, R2.2, U1.1, U1.2, U2.1 (OE)
GND: C1.2, J5.3, R1.2, U1.7 (GND), U2.10 (GND)
unnamed: D1.1 (K), R2.1
unnamed: U1.3, U1.4
unnamed: U1.8, U2.2 (D0)
unnamed: U1.9, U1.10, U1.11
VCC: C1.1, D1.2 (A), J5.4, U1.14 (VCC), U2.20 (VCC)

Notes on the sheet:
It's ROTATED! GROUND IS ABOVE!

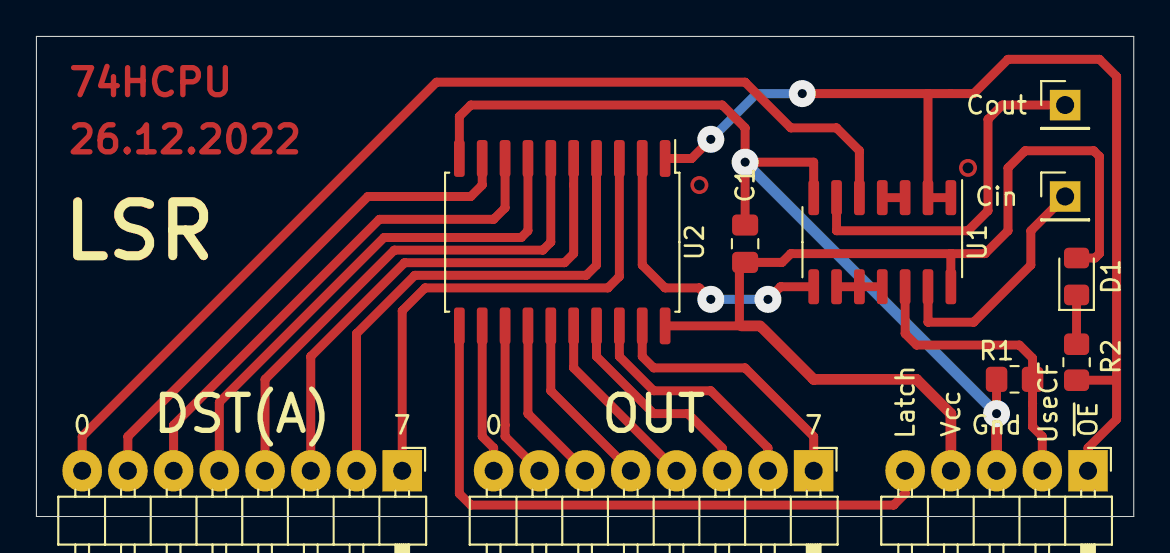
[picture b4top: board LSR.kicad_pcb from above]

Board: 2 copper layers, 61.0 x 26.7 mm, 11 parts (0 on the bottom side), 27 nets.
